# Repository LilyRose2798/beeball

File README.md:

# beeball

A PCB combining a Seeeduino XIAO, PMW3360, and Kailh Choc switches for use as a trackball mouse.

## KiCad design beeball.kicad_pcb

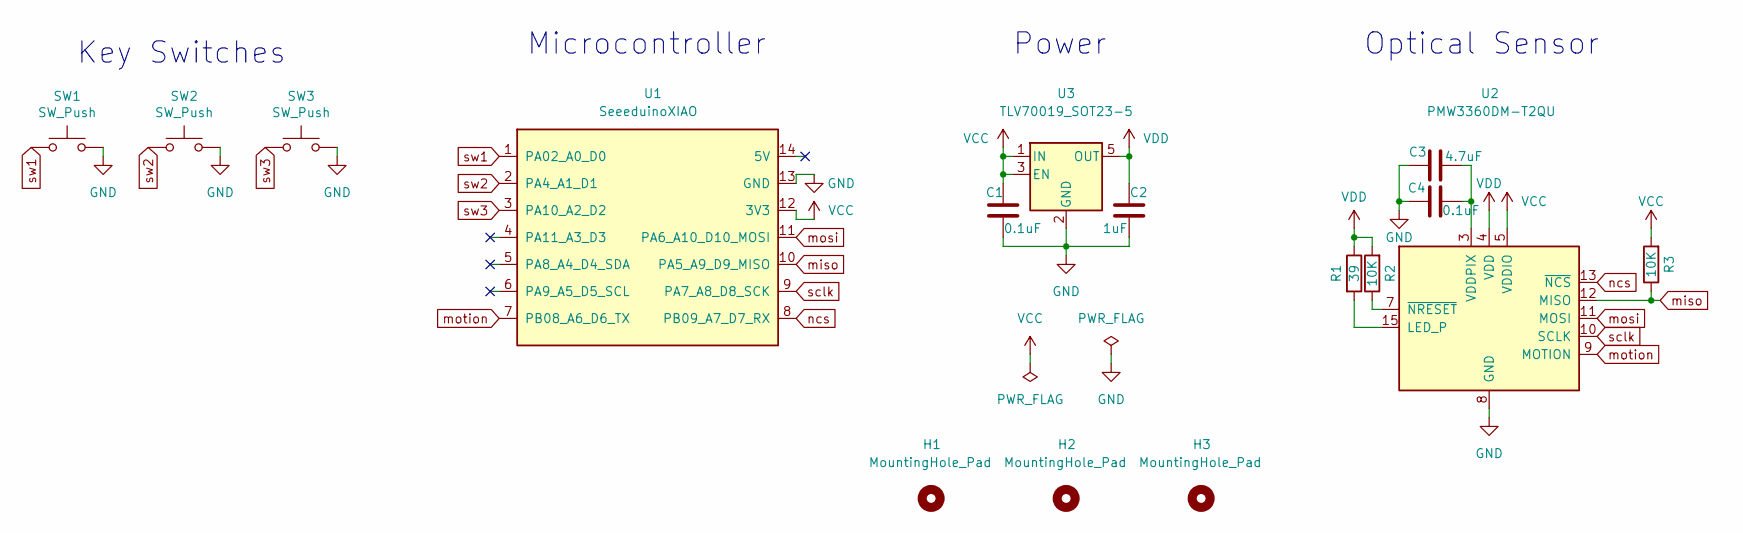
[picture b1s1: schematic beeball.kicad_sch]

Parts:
C1, C4: 0.1uF; C_0805_2012Metric
C2: 1uF; C_0805_2012Metric
C3: 4.7uF; C_0805_2012Metric
H1, H2, H3: MountingHole_Pad; MountingHole_3.2mm_M3_Pad
R1: 39; R_0805_2012Metric
R2, R3: 10K; R_0805_2012Metric
SW1, SW2, SW3: SW_Push; MX-Alps-Choc-1U
U1: SeeeduinoXIAO; Seeeduino XIAO
U2: PMW3360DM-T2QU
U3: TLV70019_SOT23-5; SOT-23-5

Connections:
GND: C1.2, C2.2, C3.2, C4.1, SW1.2, SW2.2, SW3.2, U1.13 (GND), U2.8 (GND), U3.2 (GND)
unnamed: C3.1, C4.2, U2.3 (VDDPIX)
unnamed: R1.2, U2.15 (LED_P)
unnamed: R2.1, U2.7 (~NRESET)
VCC: C1.1, R3.2, U1.12 (3V3), U2.5 (VDDIO), U3.1 (IN), U3.3 (EN)
VDD: C2.1, R1.1, R2.2, U2.4 (VDD), U3.5 (OUT)
miso: R3.1, U1.10 (PA5_A9_D9_MISO), U2.12 (MISO)
mosi: U1.11 (PA6_A10_D10_MOSI), U2.11 (MOSI)
motion: U1.7 (PB08_A6_D6_TX), U2.9 (MOTION)
ncs: U1.8 (PB09_A7_D7_RX), U2.13 (~NCS)
sclk: U1.9 (PA7_A8_D8_SCK), U2.10 (SCLK)
sw1: SW1.1, U1.1 (PA02_A0_D0)
sw2: SW2.1, U1.2 (PA4_A1_D1)
sw3: SW3.1, U1.3 (PA10_A2_D2)

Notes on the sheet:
Key Switches
Power
Microcontroller
Optical Sensor

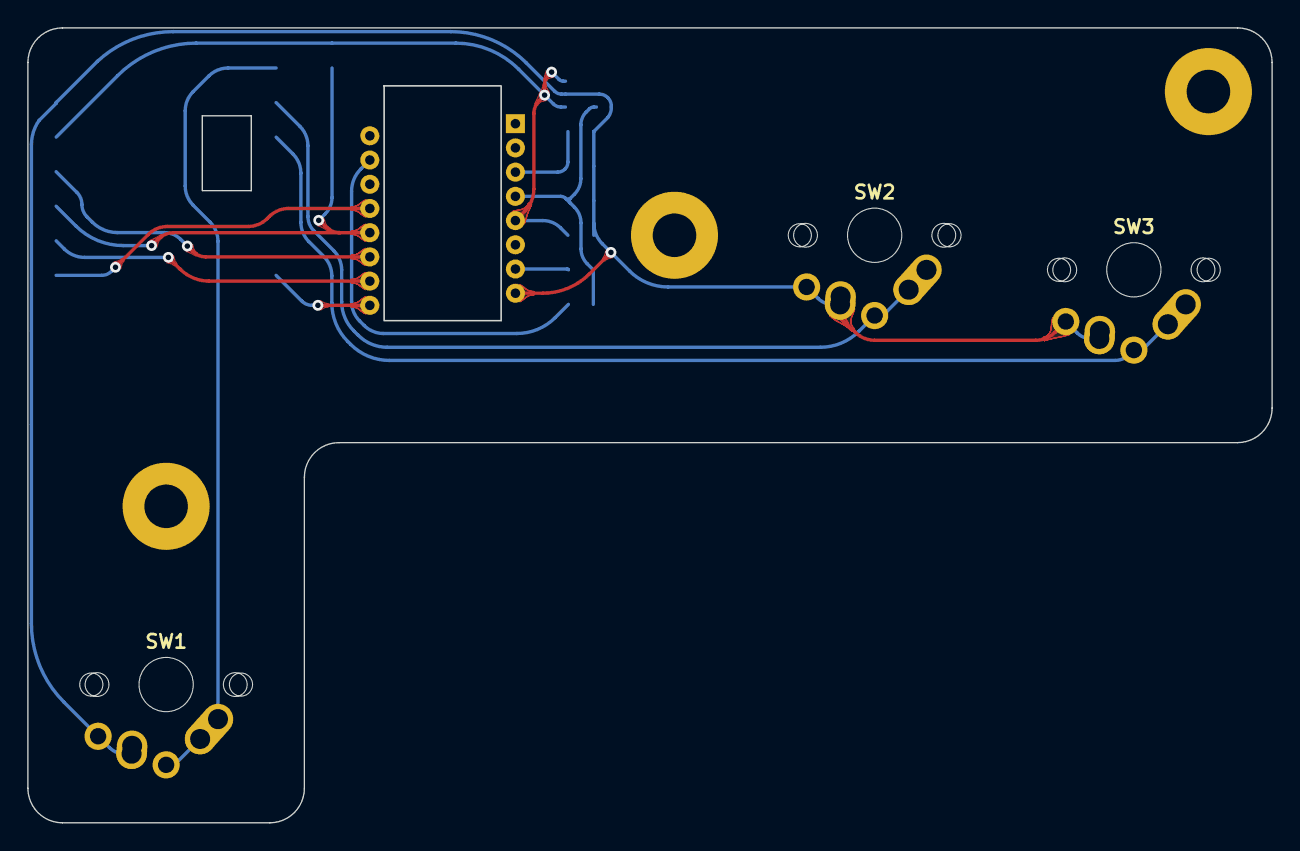
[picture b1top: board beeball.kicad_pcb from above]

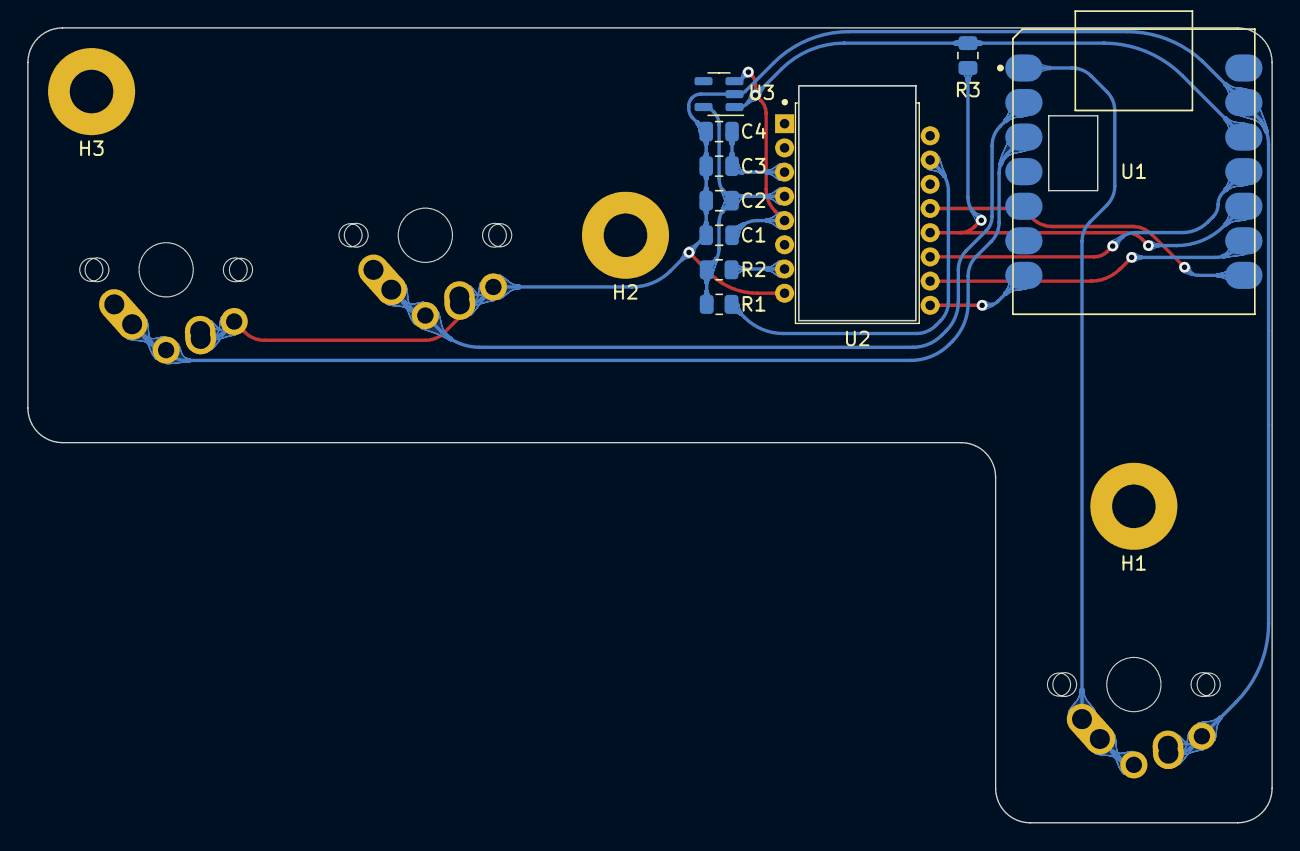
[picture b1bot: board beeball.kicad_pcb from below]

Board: 2 copper layers, 91.4 x 58.4 mm, 16 parts (13 on the bottom side), 14 nets.

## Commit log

2022-08-20 Fix battery cutout, change M2 mounting holes to M3, change Choc switch footprint to MX+Choc+Alps footprint
2022-09-14 Fix Xiao battery cutout alignment
